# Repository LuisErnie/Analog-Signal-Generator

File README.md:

# Analog-Signal-Generator
Analog Signal Generator Designed with OpAmps
Designed generates:
- Sine Wave
- Square Wave (Unipolar and Bipolar)
- Triangle Wave (Unipolar and Bipolar)
- Sawtooth
- PWM

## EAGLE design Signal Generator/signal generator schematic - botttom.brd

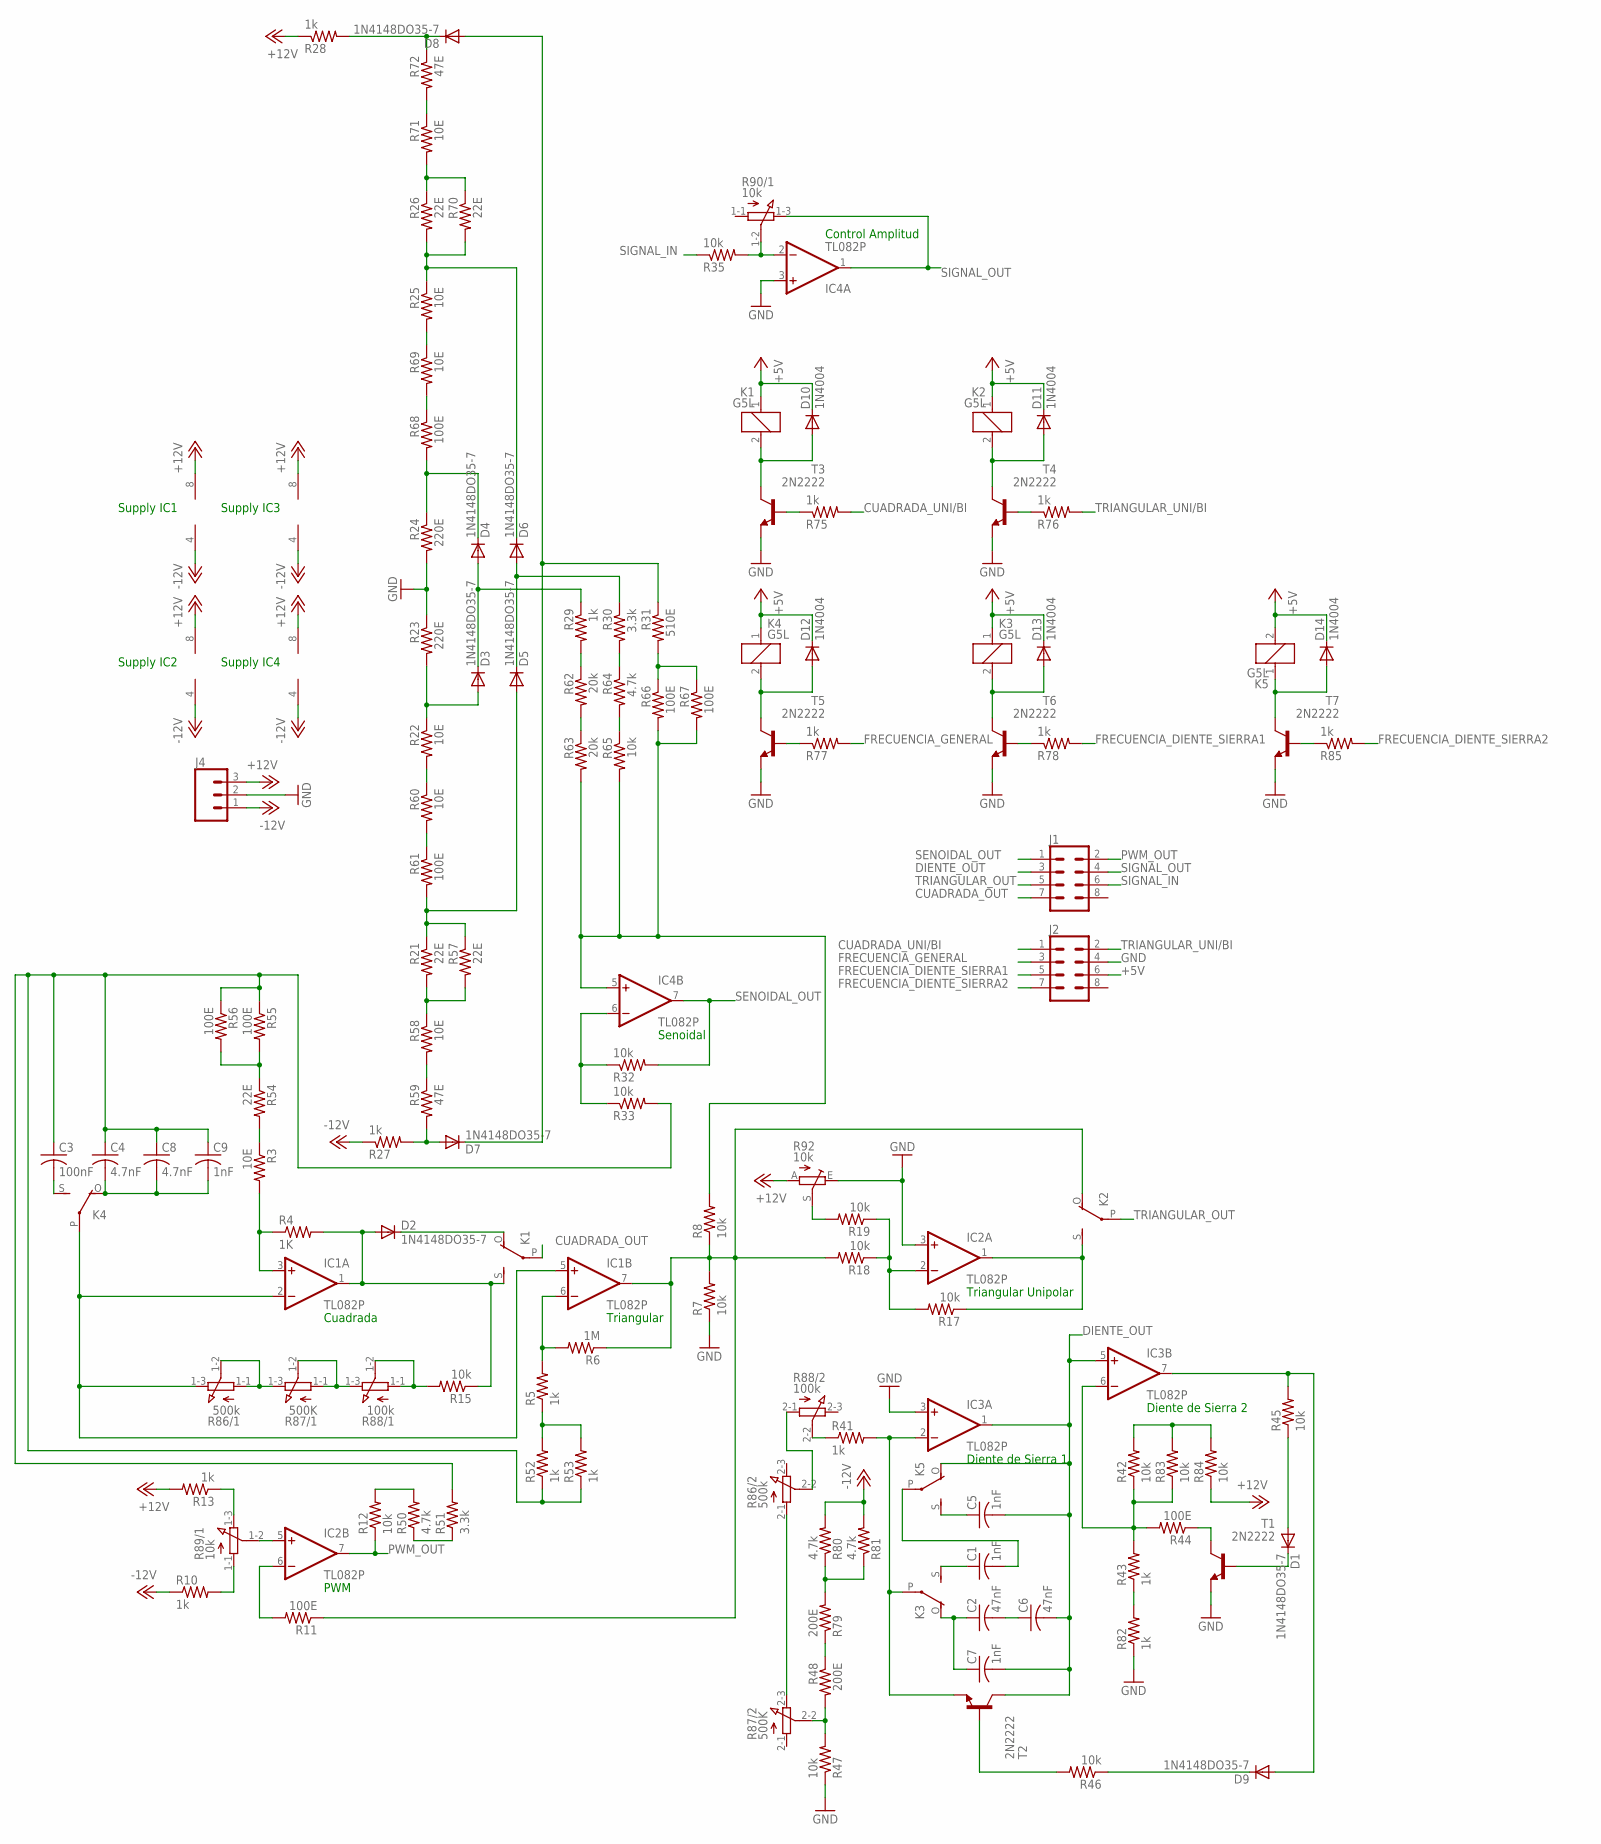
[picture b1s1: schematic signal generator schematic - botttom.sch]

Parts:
C1, C5, C7, C9: 1nF; C150-054X183
C2, C6: 47nF; C150-054X183
C3: 100nF; C150-084X183
C4, C8: 4.7nF; C102-043X133
D1, D2, D3, D4, D5, D6, D7, D8, D9: 1N4148DO35-7; DO35-7
D10, D11, D12, D13, D14: 1N4004; DO41-10
IC1, IC2, IC3, IC4: TL082P; DIL08
J1, J2: CONN_04X2; 2X4
J4: CONN_03-SCREW-5MM; SCREWTERMINAL-5MM-3
K1, K2, K3, K4, K5: G5L; G5LE
R3, R22, R25, R58, R60, R69, R71: 10E; 0207/7
R4: 1K; 0207/7
R5, R10, R13, R27, R28, R29, R41, R43, R52, R53, R75, R76, R77, R78, R82, R85: 1k; 0207/7
R6: 1M; 0207/7
R7, R8, R12, R15, R17, R18, R19, R32, R33, R35, R42, R45, R46, R47, R65, R83, R84: 10k; 0207/7
R11, R44, R55, R56, R61, R66, R67, R68: 100E; 0207/7
R21, R26, R54, R57, R70: 22E; 0207/7
R23, R24: 220E; 0207/7
R30, R51: 3.3k; 0207/7
R31: 510E; 0207/7
R48, R79: 200E; 0207/7
R50, R64, R80, R81: 4.7k; 0207/7
R59, R72: 47E; 0207/7
R62, R63: 20k; 0207/7
R86: 500k; 3RP/1610G
R87: 500K; 3RP/1610G
R88: 100k; 3RP/1610G
R89, R90: 10k; 3RP/1610G
R92: 10k; S63P
T1, T2, T3, T4, T5, T6, T7: 2N2222; TO92-EBC-OVAL

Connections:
+5V: D10.C, D11.C, D12.C, D13.C, D14.C, J2.6, K1.1, K2.1, K3.1, K4.1, K5.2
+12V: IC1.8 (V+), IC2.8 (V+), IC3.8 (V+), IC4.8 (V+), J4.3, R13.2, R28.1, R84.1, R92.A
-12V: IC1.4 (V-), IC2.4 (V-), IC3.4 (V-), IC4.4 (V-), J4.1, R10.1, R27.1, R80.2, R81.2
CUADRADA_OUT: J1.7, K1.P
CUADRADA_UNI/BI: J2.1, R75.2
DIENTE_OUT: C5.2, C6.2, C7.2, IC3.1 (OUT), IC3.5 (+IN), J1.3, K5.O, T2.C
FRECUENCIA_DIENTE_SIERRA1: J2.5, R78.2
FRECUENCIA_DIENTE_SIERRA2: J2.7, R85.2
FRECUENCIA_GENERAL: J2.3, R77.2
GND: IC2.3 (+IN), IC3.3 (+IN), IC4.3 (+IN), J2.4, J4.2, R7.1, R23.1, R24.2, R47.1, R82.1, R92.E, T1.E, T3.E, T4.E, T5.E, T6.E, T7.E
unnamed: IC1.3 (+IN), R3.2, R4.1
unnamed: C1.2, K5.P
unnamed: R58.2, R59.1
unnamed: R13.1, R89.1-3 (E)
unnamed: IC1.6 (-IN), R5.2, R6.2
unnamed: R87.1-1 (A), R87.1-2 (S), R88.1-3 (E)
unnamed: IC2.5 (+IN), R89.1-2 (S)
unnamed: R10.2, R89.1-1 (A)
unnamed: IC2.6 (-IN), R11.2
unnamed: R19.2, R92.S
unnamed: R15.2, R88.1-1 (A), R88.1-2 (S)
unnamed: D5.C, D6.A, R30.1
unnamed: D5.A, R21.1, R57.1, R61.2
unnamed: IC2.2 (-IN), R17.2, R18.1, R19.1
unnamed: D3.A, R22.1, R23.2
unnamed: D7.A, R27.2, R59.2
unnamed: D6.C, R25.1, R26.2, R70.2
unnamed: IC4.2 (-IN), R35.2, R90.1-2 (S)
unnamed: D3.C, D4.A, R29.1
unnamed: D4.C, R24.1, R68.2
unnamed: D8.C, R28.2, R72.1
unnamed: D7.C, D8.A, R31.1
unnamed: IC4.5 (+IN), R8.2, R63.2, R65.2, R66.2, R67.2
unnamed: R75.1, T3.B
unnamed: IC1.2 (-IN), IC1.5 (+IN), K4.P, R86.1-3 (E)
unnamed: R41.1, R88.2-2 (S)
unnamed: C2.1, C7.1, K3.O
unnamed: IC4.6 (-IN), R32.1, R33.1
unnamed: C1.1, K3.S
unnamed: R47.2, R48.2, R87.2-2 (S)
unnamed: R86.2-1 (A), R87.2-3 (E)
unnamed: R46.2, T2.B
unnamed: D1.C, T1.B
unnamed: IC3.6 (-IN), R42.1, R43.2, R44.2, R83.1
unnamed: R44.1, T1.C
unnamed: D1.A, R45.1
unnamed: D9.A, IC3.7 (OUT), R45.2
unnamed: D9.C, R46.1
unnamed: R12.2, R50.2
unnamed: R50.1, R51.1
unnamed: R5.1, R52.2, R53.2
unnamed: C4.2, C8.2, C9.2, K4.O
unnamed: R3.1, R54.2
unnamed: C3.2, K4.S
unnamed: R54.1, R55.2, R56.2
unnamed: R21.2, R57.2, R58.1
unnamed: C3.1, C4.1, C8.1, C9.1, R33.2, R51.2, R52.1, R53.1, R55.1, R56.1
unnamed: R60.2, R61.1
unnamed: R22.2, R60.1
unnamed: R29.2, R62.1
unnamed: R62.2, R63.1
unnamed: R64.2, R65.1
unnamed: R30.2, R64.1
unnamed: R25.2, R69.1
unnamed: R31.2, R66.1, R67.1
unnamed: R68.1, R69.2
unnamed: R71.1, R72.2
unnamed: R26.1, R70.1, R71.2
unnamed: D2.C, K1.O
unnamed: D10.A, K1.2, T3.C
unnamed: R76.1, T4.B
unnamed: D11.A, K2.2, T4.C
unnamed: R77.1, T5.B
unnamed: D12.A, K4.2, T5.C
unnamed: R78.1, T6.B
unnamed: D13.A, K3.2, T6.C
unnamed: IC3.2 (-IN), K3.P, R41.2, T2.E
unnamed: R48.1, R79.1
unnamed: C5.1, K5.S
unnamed: R79.2, R80.1, R81.1
unnamed: R43.1, R82.2
unnamed: C2.2, C6.1
unnamed: R42.2, R83.2, R84.2
unnamed: R86.1-1 (A), R86.1-2 (S), R87.1-3 (E)
unnamed: R85.1, T7.B
unnamed: D14.A, K5.1, T7.C
unnamed: R86.2-2 (S), R88.2-1 (A)
unnamed: D2.A, IC1.1 (OUT), K1.S, R4.2, R15.1
unnamed: IC1.7 (OUT), K2.O, R6.1, R7.2, R8.1, R11.1, R18.2
unnamed: IC2.1 (OUT), K2.S, R17.1
PWM_OUT: IC2.7 (OUT), J1.2, R12.1
SENOIDAL_OUT: IC4.7 (OUT), J1.1, R32.2
SIGNAL_IN: J1.6, R35.1
SIGNAL_OUT: IC4.1 (OUT), J1.4, R90.1-3 (E)
TRIANGULAR_OUT: J1.5, K2.P
TRIANGULAR_UNI/BI: J2.2, R76.2

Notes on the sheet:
Supply IC1
Supply IC2
Supply IC3
Supply IC4
Cuadrada
Triangular
PWM
Triangular Unipolar
Senoidal
Diente de Sierra 1
Diente de Sierra 2
Control Amplitud

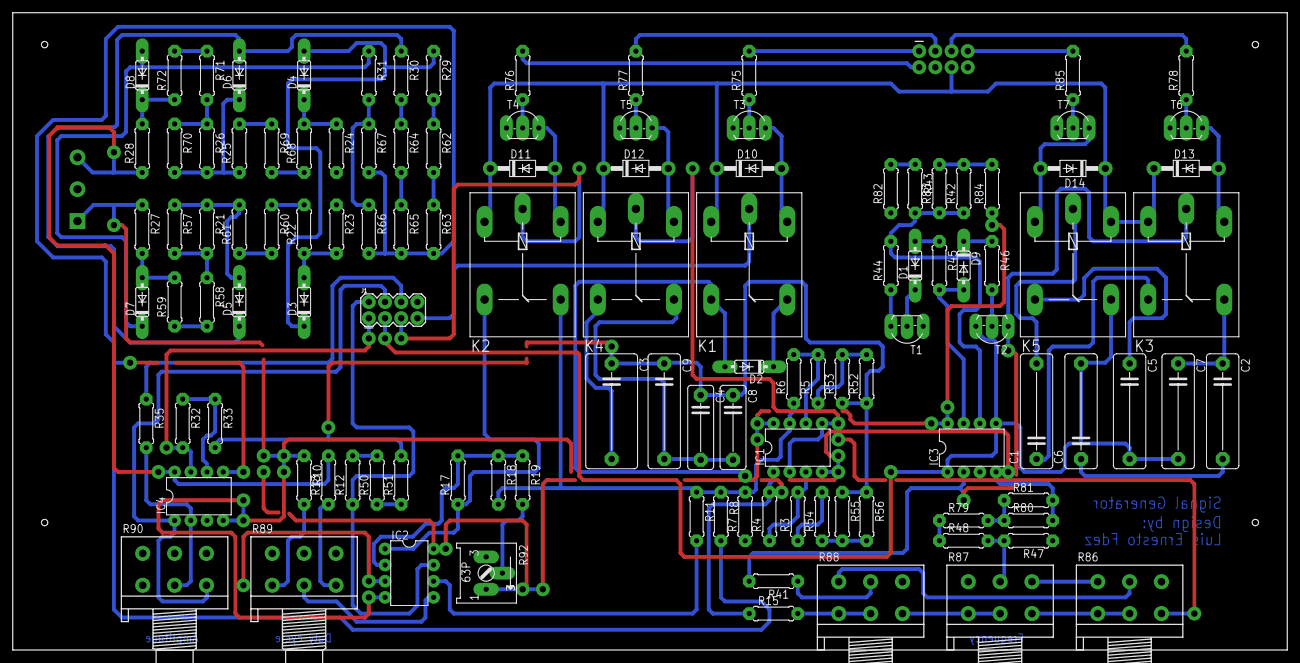
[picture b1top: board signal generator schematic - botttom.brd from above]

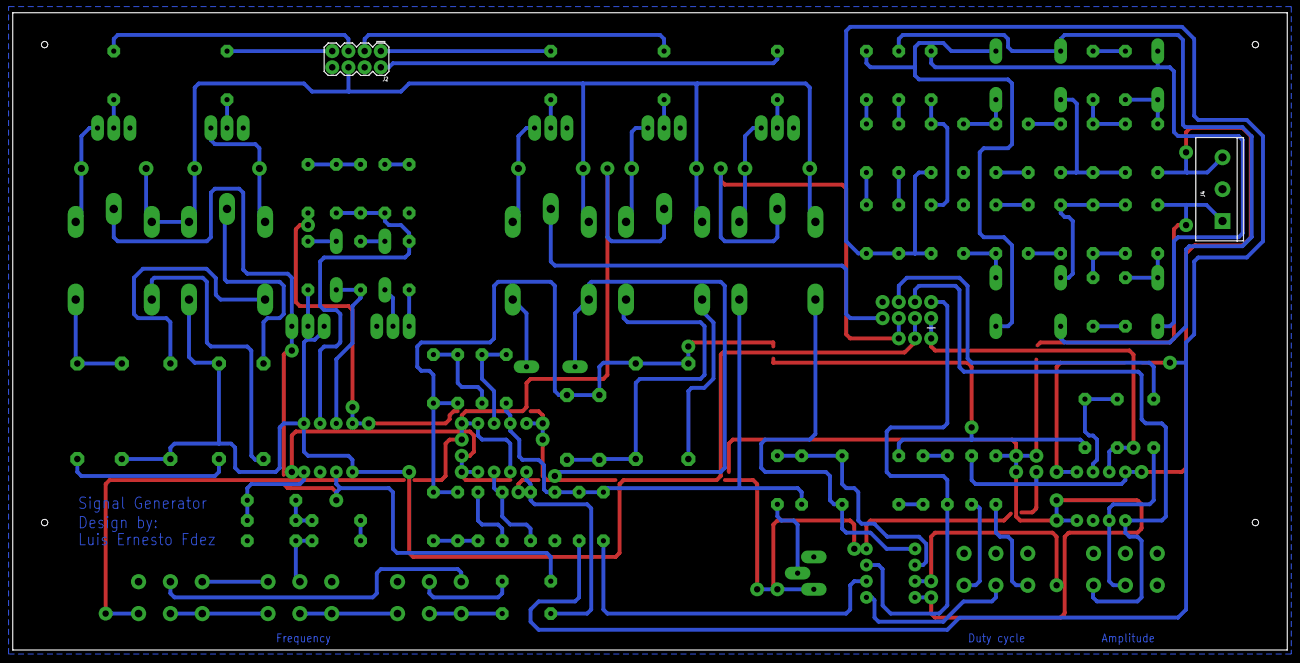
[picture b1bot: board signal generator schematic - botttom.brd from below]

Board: 2 copper layers, 200.0 x 100.0 mm, 118 parts (2 on the bottom side), 96 nets.

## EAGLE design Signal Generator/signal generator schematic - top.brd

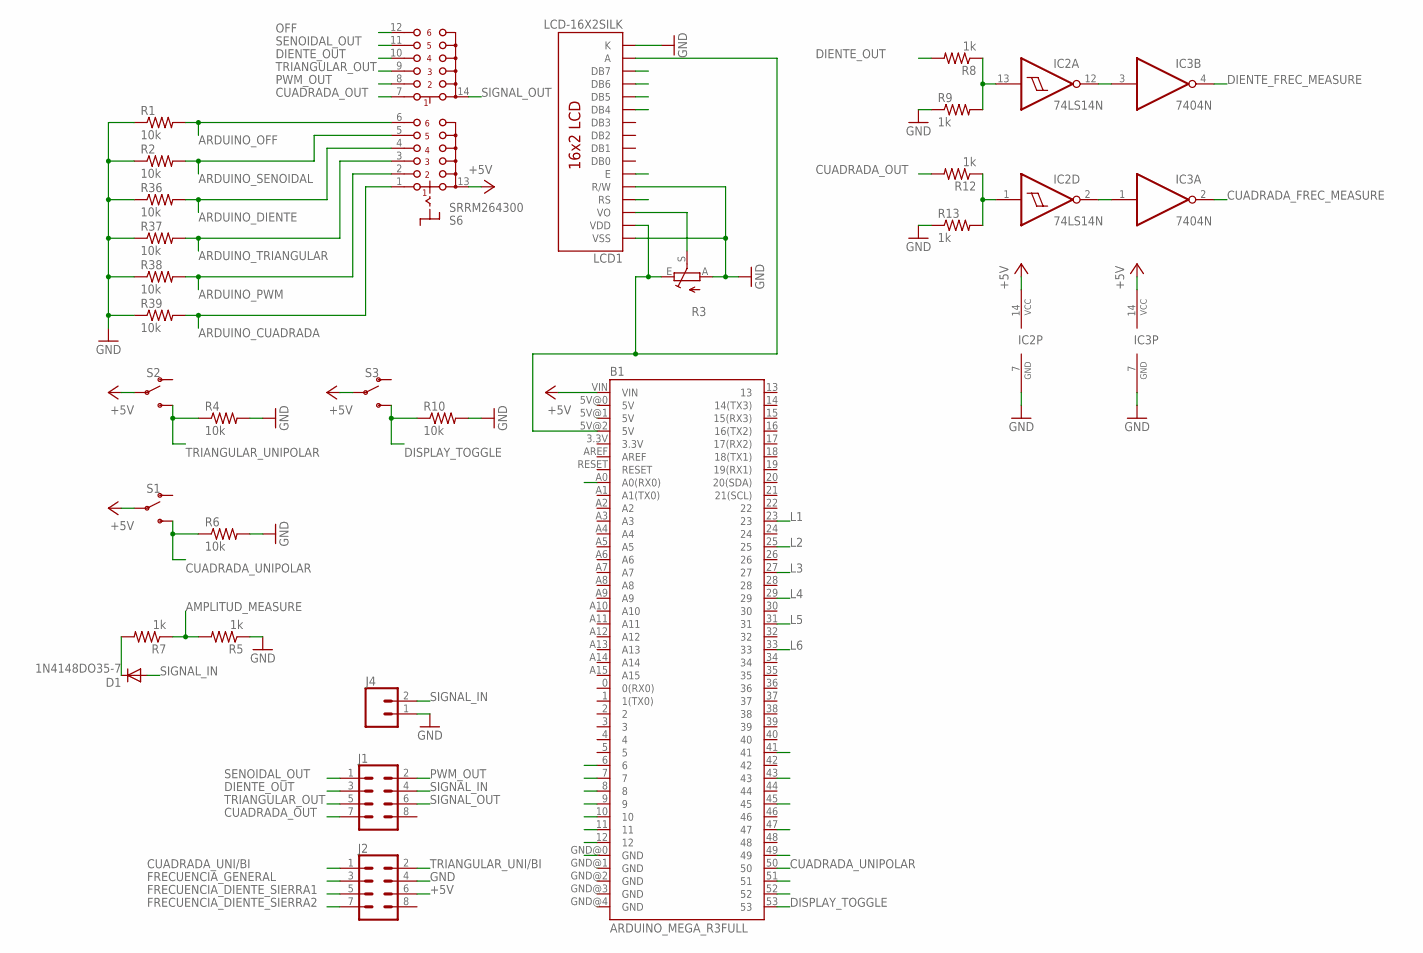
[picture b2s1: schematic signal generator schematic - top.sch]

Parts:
B1: ARDUINO_MEGA_R3FULL; ARDUINO_MEGA
D1: 1N4148DO35-7; DO35-7
IC2: 74LS14N; DIL14
IC3: 7404N; DIL14
J1, J2: CONN_04X2; 2X4
J4: CONN_025MM; SCREWTERMINAL-5MM-2
LCD1: LCD-16X2SILK; LCD-16X2
R1, R2, R4, R6, R10, R36, R37, R38, R39: 10k; 0207/7
R3: TRIM_EU-S63P; S63P
R5, R7, R8, R9, R12, R13: 1k; 0207/7
S1, S2, S3: SWITCH-SPDT-PTH-11.6X4.0MM; SWITCH_SPDT_PTH_11.6X4.0MM
S6: SRRM264300

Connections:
+5V: B1.VIN, IC2.14 (VCC), IC3.14 (VCC), J2.6, S1.2, S2.2, S3.2, S6.13 (A)
AMPLITUD_MEASURE: R5.2, R7.1
AN: B1.A0 (A0(RX0))
ARDUINO_CUADRADA: B1.41, R39.2, S6.1 (A1)
ARDUINO_DIENTE: B1.47, R36.2, S6.4 (A4)
ARDUINO_OFF: B1.51, R1.2, S6.6 (A6)
ARDUINO_PWM: B1.43, R38.2, S6.2 (A2)
ARDUINO_SENOIDAL: B1.49, R2.2, S6.5 (A5)
ARDUINO_TRIANGULAR: B1.45, R37.2, S6.3 (A3)
CUADRADA_FREC_MEASURE: B1.6, IC3.2 (O)
CUADRADA_OUT: J1.7, R12.2, S6.7 (C1)
CUADRADA_UNI/BI: B1.9, J2.1
CUADRADA_UNIPOLAR: B1.50, R6.1, S1.3 (S)
DIENTE_FREC_MEASURE: B1.7, IC3.4 (O)
DIENTE_OUT: J1.3, R8.2, S6.10 (C4)
DISPLAY_TOGGLE: B1.53, R10.1, S3.3 (S)
FRECUENCIA_DIENTE_SIERRA1: B1.11, J2.5
FRECUENCIA_DIENTE_SIERRA2: B1.12, J2.7
FRECUENCIA_GENERAL: B1.10, J2.3
GND: B1.GND@0 (GND), IC2.7 (GND), IC3.7 (GND), J2.4, J4.1, LCD1.1 (VSS), LCD1.5 (R/W), LCD1.16 (K), R1.1, R2.1, R3.A, R4.2, R5.1, R6.2, R9.1, R10.2, R13.1, R36.1, R37.1, R38.1, R39.1
L1: B1.23, LCD1.14 (DB7)
L2: B1.25, LCD1.13 (DB6)
L3: B1.27, LCD1.12 (DB5)
L4: B1.29, LCD1.11 (DB4)
L5: B1.31, LCD1.6 (E)
L6: B1.33, LCD1.4 (RS)
unnamed: B1.5V@2 (5V), LCD1.2 (VDD), LCD1.15 (A), R3.E
unnamed: LCD1.3 (VO), R3.S
unnamed: D1.C, R7.2
unnamed: IC2.12 (O), IC3.3 (I)
unnamed: IC2.2 (O), IC3.1 (I)
unnamed: IC2.13 (I), R8.1, R9.2
unnamed: IC2.1 (I), R12.1, R13.2
OFF: S6.12 (C6)
PWM_OUT: J1.2, S6.8 (C2)
SENOIDAL_OUT: J1.1, S6.11 (C5)
SIGNAL_IN: D1.A, J1.4, J4.2
SIGNAL_OUT: J1.6, S6.14 (C)
TRIANGULAR_OUT: J1.5, S6.9 (C3)
TRIANGULAR_UNI/BI: B1.8, J2.2
TRIANGULAR_UNIPOLAR: B1.52, R4.1, S2.3 (S)

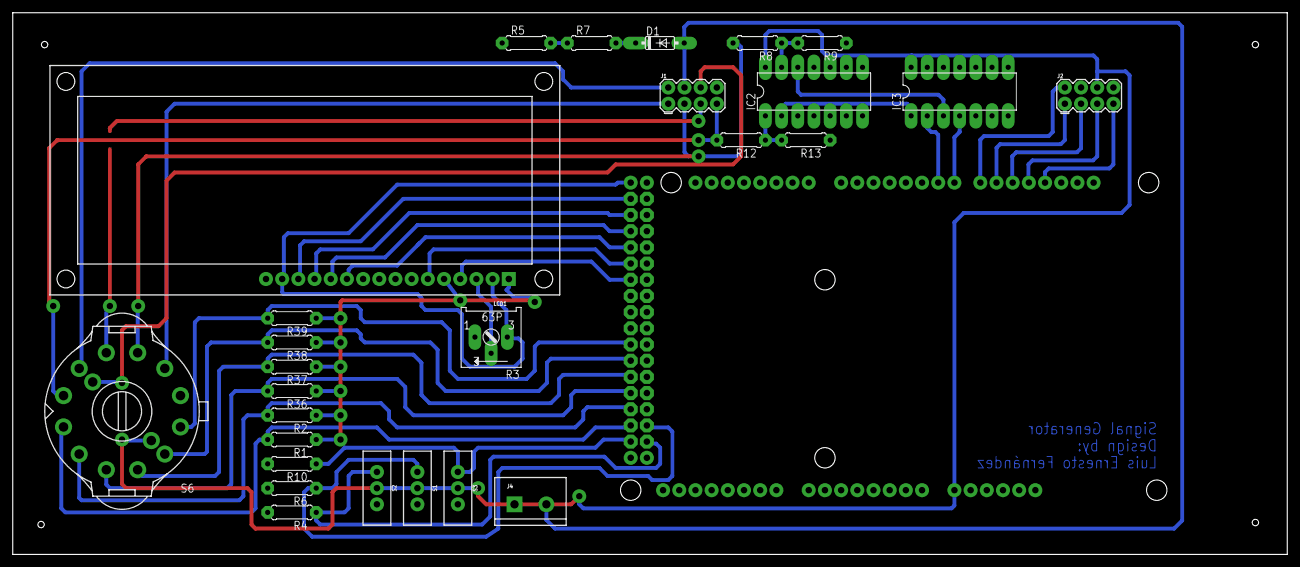
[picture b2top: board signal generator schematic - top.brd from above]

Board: 2 copper layers, 200.0 x 85.0 mm, 28 parts (1 on the bottom side), 39 nets.

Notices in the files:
parts and their libraries:
SparkFun-Connectors: Licensing: Creative Commons ShareAlike 4.0 International - https://creativecommons.org/licenses/by-sa/4.0
